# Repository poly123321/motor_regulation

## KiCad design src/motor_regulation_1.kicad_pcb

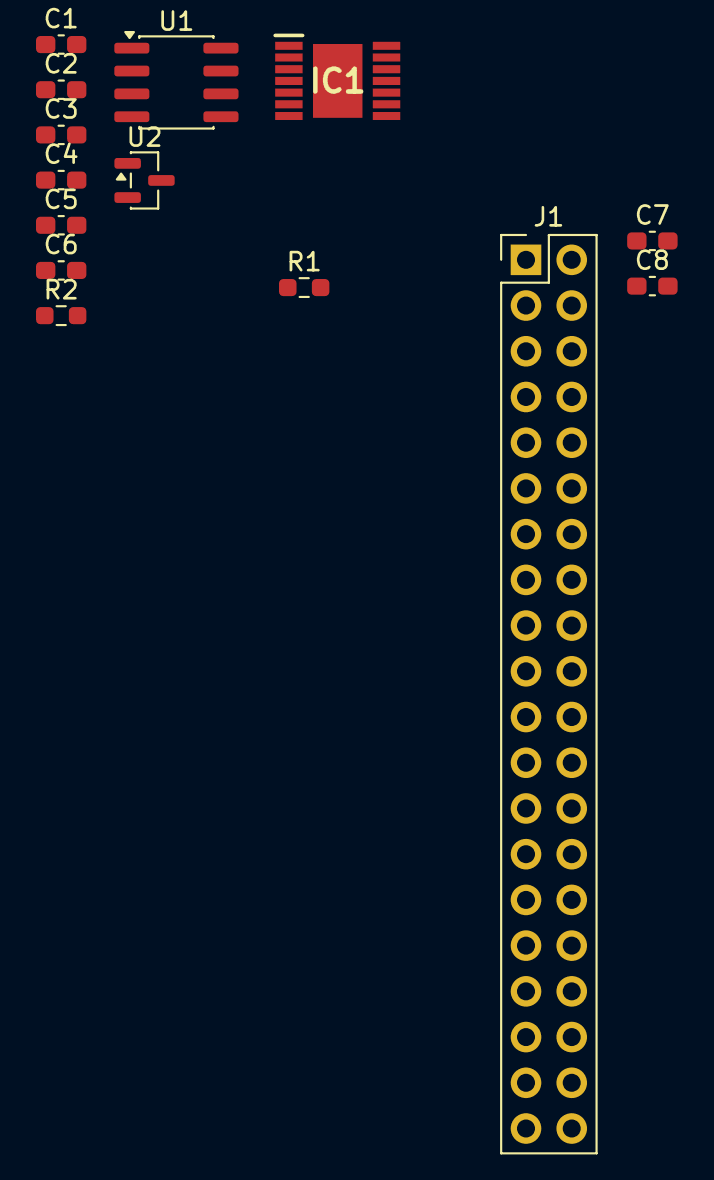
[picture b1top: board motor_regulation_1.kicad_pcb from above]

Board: 2 copper layers, 14 parts (0 on the bottom side), 8 nets, no tracks yet.

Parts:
C1, C3, C5, C7: 100n; C_0603_1608Metric_Pad1.08x0.95mm_HandSolder
C2, C4, C6, C8: 1u; C_0603_1608Metric_Pad1.08x0.95mm_HandSolder
IC1: TLE94004EP; SOP65P600X115-15N
J1: Raspberry_Pi_2_3; PinHeader_2x20_P2.54mm_Vertical
R1: R; R_0603_1608Metric_Pad0.98x0.95mm_HandSolder
R2: 0R1; R_0603_1608Metric_Pad0.98x0.95mm_HandSolder
U1: INA240A1D; SOIC-8_3.9x4.9mm_P1.27mm
U2: TPS7A0533PDBZ; SOT-23

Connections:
5V: C6.1, U2.3 (VI)
+3.3VA: C1.1, C2.1, C3.1, C4.1, C5.1, C7.1, C8.1, IC1.14 (VDD), U1.6 (V+), U2.2 (VO)
GND: C1.2, C2.2, C3.2, C4.2, C5.2, C6.2, C7.2, C8.2, U1.2 (GND), U1.4 (GND)
unnamed: J1.1 (3V3), J1.17 (3V3)
unnamed: J1.2 (5V), J1.4 (5V)
unnamed: J1.6 (GND), J1.9 (GND), J1.14 (GND), J1.20 (GND), J1.25 (GND), J1.30 (GND), J1.34 (GND), J1.39 (GND)
unnamed: R2.1, U1.8 (+)
unnamed: R2.2, U1.1 (-)
